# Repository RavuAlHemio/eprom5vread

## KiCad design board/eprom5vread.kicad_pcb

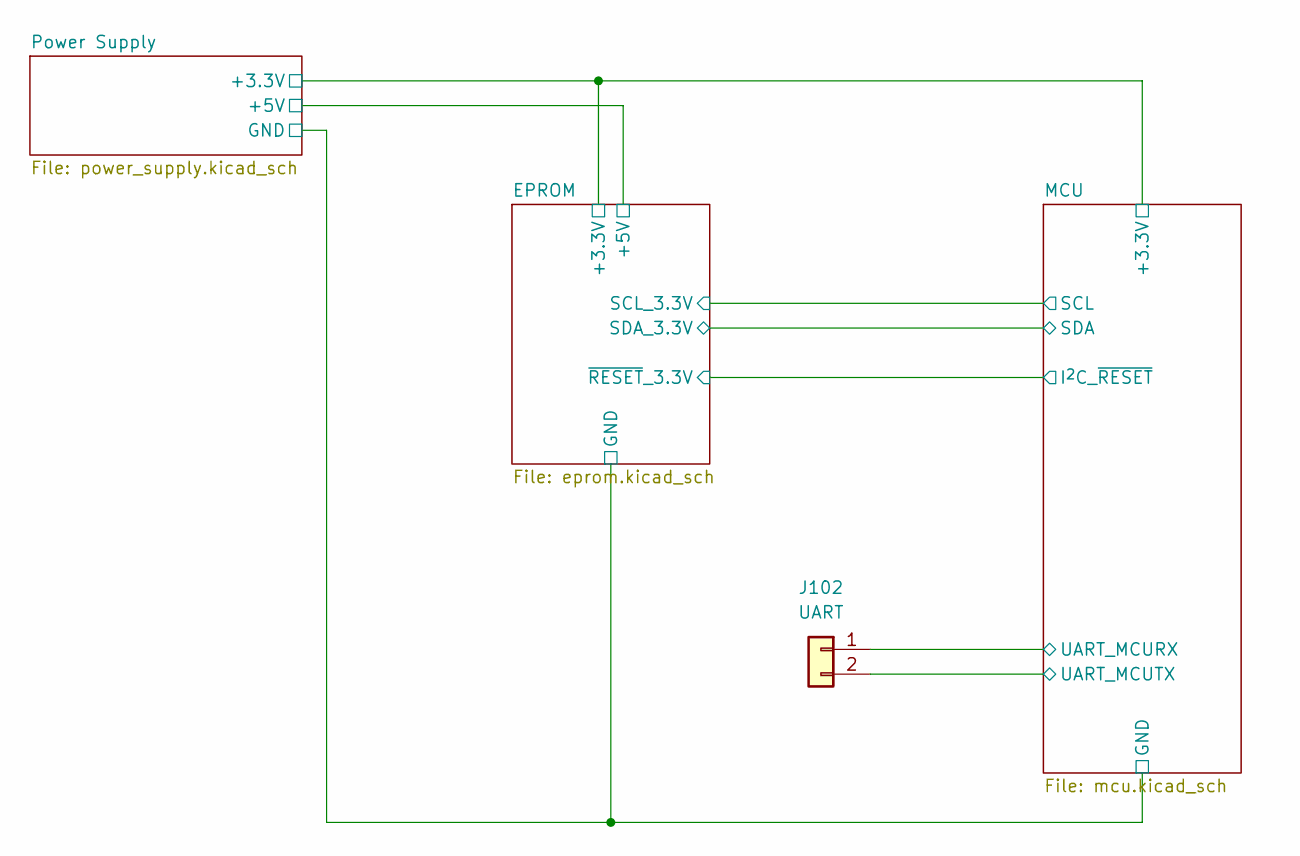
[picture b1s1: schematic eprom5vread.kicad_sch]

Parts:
J102: UART; PinHeader_2x01_P2.54mm_Vertical_SMD; LCSC C2884014

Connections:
/MCU/UART_MCURX: J102.1; also elsewhere on the board
/MCU/UART_MCUTX: J102.2; also elsewhere on the board

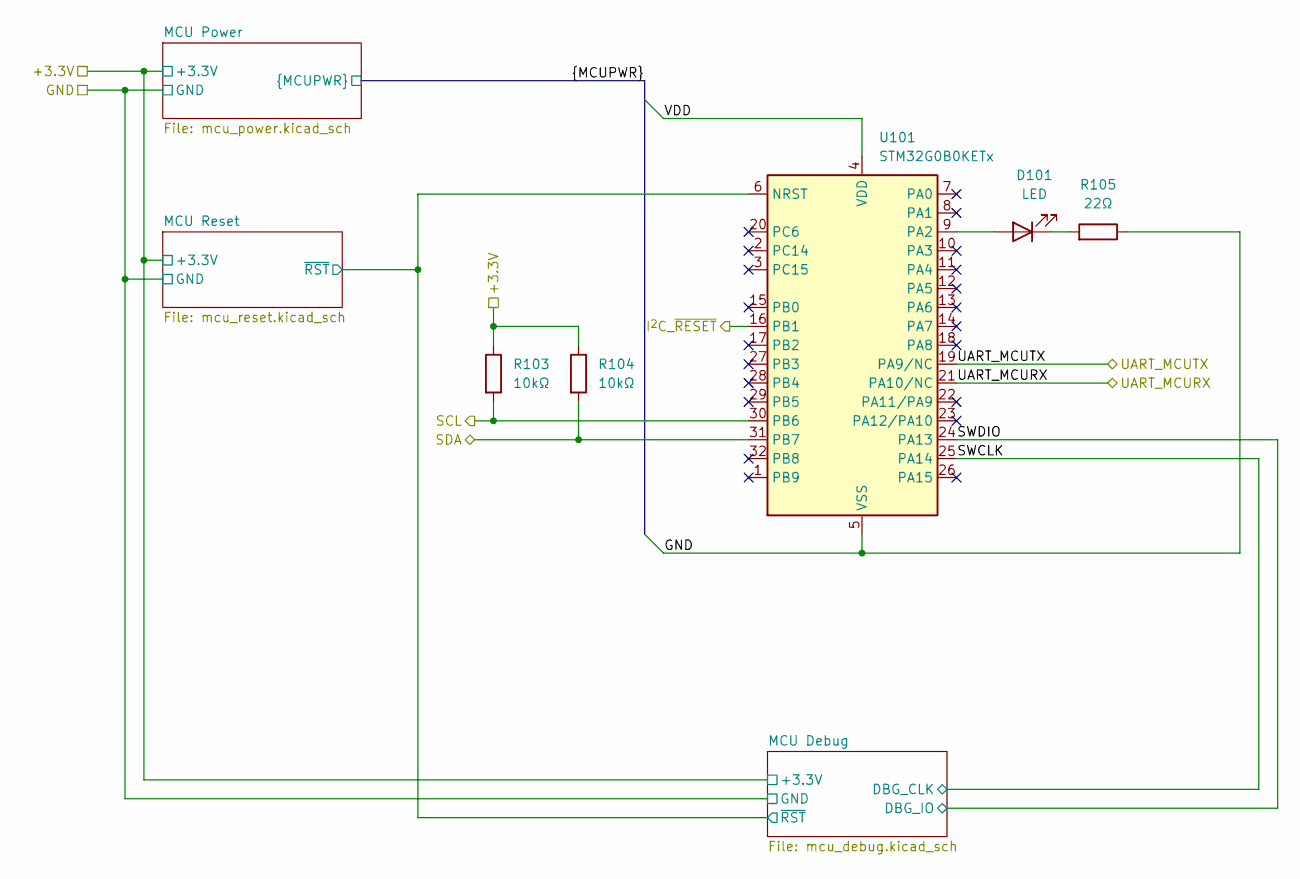
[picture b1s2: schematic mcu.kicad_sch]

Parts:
D101: LED; LED_0805_2012Metric
R103, R104: 10kΩ; R_0402_1005Metric; LCSC C25744
R105: 22Ω; R_0402_1005Metric; LCSC C25092
U101: STM32G0B0KETx; LQFP-32_7x7mm_P0.8mm; LCSC C2826978

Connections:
/EPROM/+3.3V: R103.1, R104.1; also elsewhere on the board
/EPROM/GND: R105.1, U101.5 (VSS); also elsewhere on the board
/EPROM/SCL_3.3V: R103.2, U101.30 (PB6); also elsewhere on the board
/EPROM/SDA_3.3V: R104.2, U101.31 (PB7); also elsewhere on the board
/EPROM/~RESET_3.3V: U101.16 (PB1); also elsewhere on the board
/MCU/MCU Debug/~RST: U101.6 (NRST); also elsewhere on the board
/MCU/SWCLK: U101.25 (PA14); also elsewhere on the board
/MCU/SWDIO: U101.24 (PA13); also elsewhere on the board
/MCU/UART_MCURX: U101.21 (PA10/NC); also elsewhere on the board
/MCU/UART_MCUTX: U101.19 (PA9/NC); also elsewhere on the board
/MCU/VDD: U101.4 (VDD); also elsewhere on the board
unnamed: D101.2 (A), U101.9 (PA2)
unnamed: D101.1 (K), R105.2

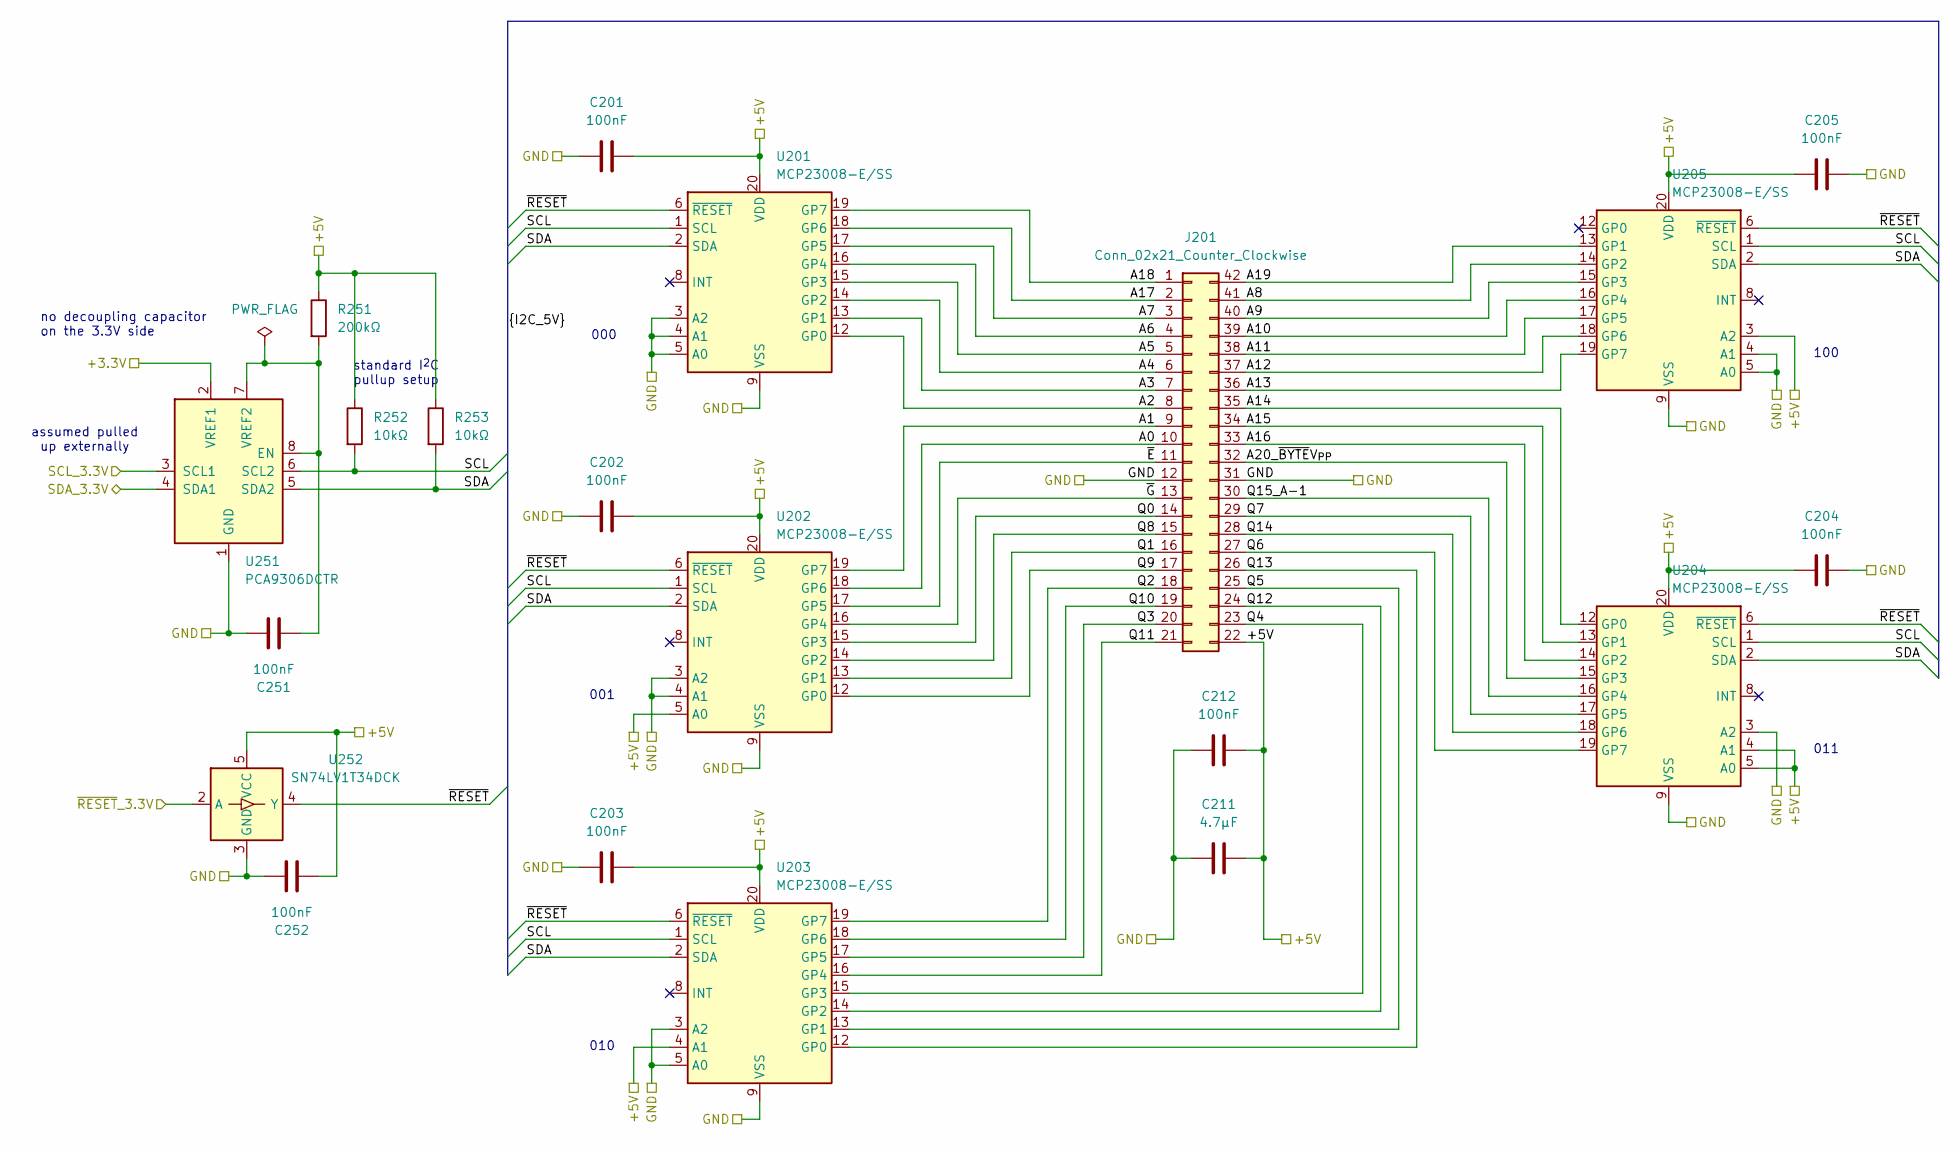
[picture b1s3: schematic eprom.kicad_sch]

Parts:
C201, C202, C203, C204, C205, C212, C251, C252: 100nF; C_0402_1005Metric; LCSC C307331
C211: 4.7µF; C_0402_1005Metric; LCSC C23733
J201: Conn_02x21_Counter_Clockwise; DIP-42_W15.24mm_Socket
R251: 200kΩ; R_0402_1005Metric; LCSC C25764
R252, R253: 10kΩ; R_0402_1005Metric; LCSC C25744
U201, U202, U203, U204, U205: MCP23008-E/SS; SSOP-20_5.3x7.2mm_P0.65mm; LCSC C148011
U251: PCA9306DCTR; SSOP-8_2.95x2.8mm_P0.65mm; LCSC C123752
U252: SN74LV1T34DCK; SOT-353_SC-70-5; LCSC C78541

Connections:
/EPROM/+3.3V: U251.2 (VREF1); also elsewhere on the board
/EPROM/+5V: C201.2, C202.2, C203.2, C204.2, C205.2, C211.2, C212.2, C252.2, J201.22, R251.1, R252.1, R253.1, U201.20 (VDD), U202.5 (A0), U202.20 (VDD), U203.4 (A1), U203.20 (VDD), U204.4 (A1), U204.5 (A0), U204.20 (VDD), U205.3 (A2), U205.20 (VDD), U252.5 (VCC); also elsewhere on the board
/EPROM/A0: J201.10, U202.18 (GP6)
/EPROM/A1: J201.9, U202.19 (GP7)
/EPROM/A2: J201.8, U201.12 (GP0)
/EPROM/A3: J201.7, U201.13 (GP1)
/EPROM/A4: J201.6, U201.14 (GP2)
/EPROM/A5: J201.5, U201.15 (GP3)
/EPROM/A6: J201.4, U201.16 (GP4)
/EPROM/A7: J201.3, U201.17 (GP5)
/EPROM/A8: J201.41, U205.14 (GP2)
/EPROM/A9: J201.40, U205.15 (GP3)
/EPROM/A10: J201.39, U205.16 (GP4)
/EPROM/A11: J201.38, U205.17 (GP5)
/EPROM/A12: J201.37, U205.18 (GP6)
/EPROM/A13: J201.36, U205.19 (GP7)
/EPROM/A14: J201.35, U204.12 (GP0)
/EPROM/A15: J201.34, U204.13 (GP1)
/EPROM/A16: J201.33, U204.14 (GP2)
/EPROM/A17: J201.2, U201.18 (GP6)
/EPROM/A18: J201.1, U201.19 (GP7)
/EPROM/A19: J201.42, U205.13 (GP1)
/EPROM/A20_~BYTEV_{PP}: J201.32, U204.15 (GP3)
/EPROM/GND: C201.1, C202.1, C203.1, C204.1, C205.1, C211.1, C212.1, C251.1, C252.1, J201.12, J201.31, U201.3 (A2), U201.4 (A1), U201.5 (A0), U201.9 (VSS), U202.3 (A2), U202.4 (A1), U202.9 (VSS), U203.3 (A2), U203.5 (A0), U203.9 (VSS), U204.3 (A2), U204.9 (VSS), U205.4 (A1), U205.5 (A0), U205.9 (VSS), U251.1 (GND), U252.3 (GND); also elsewhere on the board
/EPROM/Q0: J201.14, U202.15 (GP3)
/EPROM/Q1: J201.16, U202.13 (GP1)
/EPROM/Q2: J201.18, U203.19 (GP7)
/EPROM/Q3: J201.20, U203.17 (GP5)
/EPROM/Q4: J201.23, U203.15 (GP3)
/EPROM/Q5: J201.25, U203.13 (GP1)
/EPROM/Q6: J201.27, U204.19 (GP7)
/EPROM/Q7: J201.29, U204.17 (GP5)
/EPROM/Q8: J201.15, U202.14 (GP2)
/EPROM/Q9: J201.17, U202.12 (GP0)
/EPROM/Q10: J201.19, U203.18 (GP6)
/EPROM/Q11: J201.21, U203.16 (GP4)
/EPROM/Q12: J201.24, U203.14 (GP2)
/EPROM/Q13: J201.26, U203.12 (GP0)
/EPROM/Q14: J201.28, U204.18 (GP6)
/EPROM/Q15_A-1: J201.30, U204.16 (GP4)
/EPROM/SCL: R252.2, U201.1 (SCL), U202.1 (SCL), U203.1 (SCL), U204.1 (SCL), U205.1 (SCL), U251.6 (SCL2)
/EPROM/SCL_3.3V: U251.3 (SCL1); also elsewhere on the board
/EPROM/SDA: R253.2, U201.2 (SDA), U202.2 (SDA), U203.2 (SDA), U204.2 (SDA), U205.2 (SDA), U251.5 (SDA2)
/EPROM/SDA_3.3V: U251.4 (SDA1); also elsewhere on the board
/EPROM/~E: J201.11, U202.17 (GP5)
/EPROM/~G: J201.13, U202.16 (GP4)
/EPROM/~RESET: U201.6 (~RESET), U202.6 (~RESET), U203.6 (~RESET), U204.6 (~RESET), U205.6 (~RESET), U252.4 (Y)
/EPROM/~RESET_3.3V: U252.2 (A); also elsewhere on the board
unnamed: C251.2, R251.2, U251.7 (VREF2), U251.8 (EN)

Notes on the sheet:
standard I^{2}C pullup setup
001
no decoupling capacitor on the 3.3V side
000
011
010
100
assumed pulled up externally

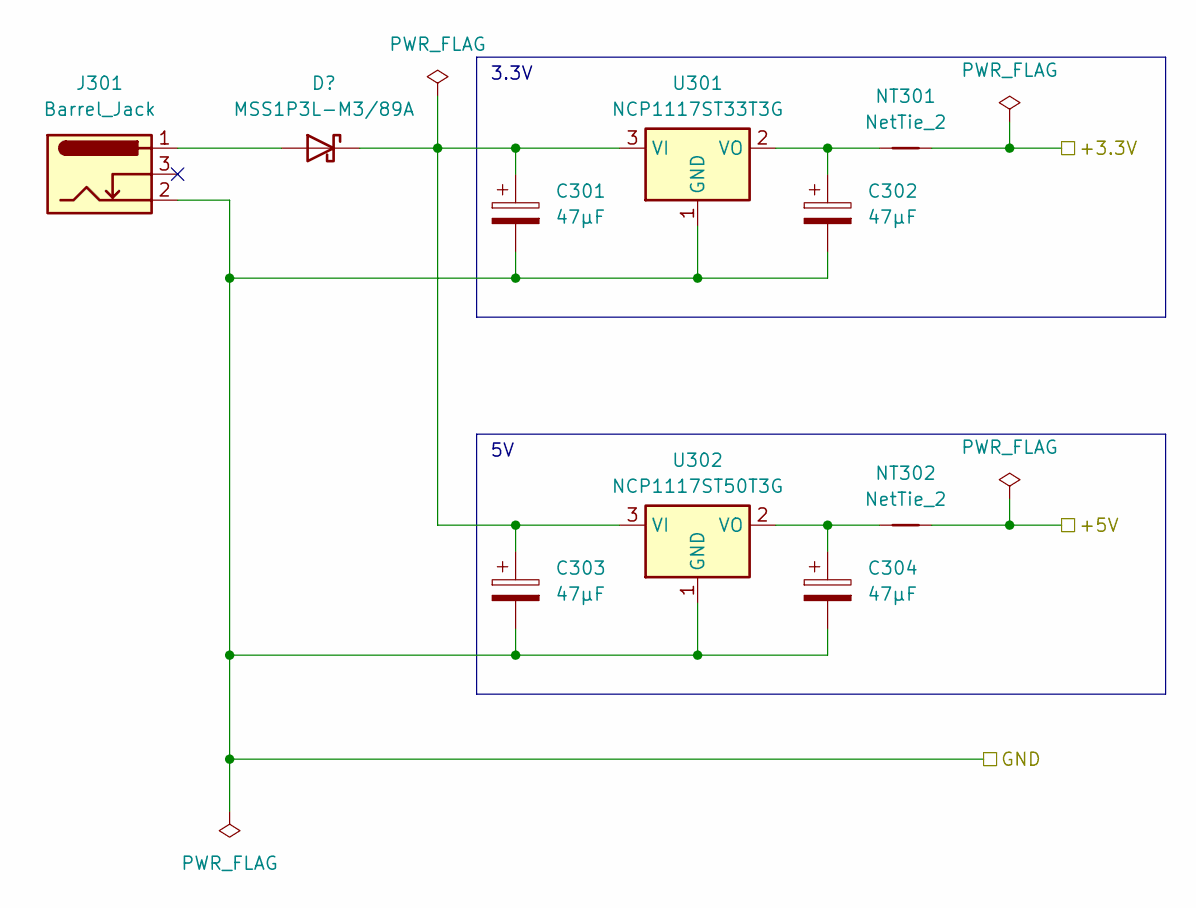
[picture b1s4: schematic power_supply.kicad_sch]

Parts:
C301, C302, C303, C304: 47µF; CP_EIA-7343-31_Kemet-D; LCSC C122333
D301: MSS1P3L-M3/89A; D_MicroSMP_AK; LCSC C144285
J301: Barrel_Jack; BarrelJack_CUI_PJ-036AH-SMT_Horizontal; LCSC C9900024875
NT301, NT302: NetTie_2; NetTie-2_SMD_Pad0.5mm
U301: NCP1117ST33T3G; SOT-223-3_TabPin2; LCSC C26537
U302: NCP1117ST50T3G; SOT-223-3_TabPin2; LCSC C17314

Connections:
/EPROM/+3.3V: NT301.2; also elsewhere on the board
/EPROM/+5V: NT302.2; also elsewhere on the board
/EPROM/GND: C301.2, C302.2, C303.2, C304.2, J301.2, U301.1 (GND), U302.1 (GND); also elsewhere on the board
unnamed: D301.2 (A), J301.1
unnamed: C301.1, C303.1, D301.1 (K), U301.3 (VI), U302.3 (VI)
unnamed: C302.1, NT301.1, U301.2 (VO)
unnamed: C304.1, NT302.1, U302.2 (VO)

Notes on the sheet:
3.3V

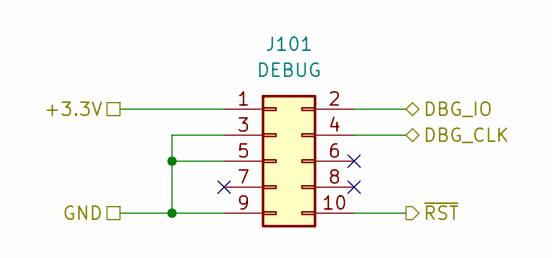
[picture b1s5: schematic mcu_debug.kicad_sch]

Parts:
J101: DEBUG; PinHeader_2x05_P1.27mm_Vertical_SMD; LCSC C5250218

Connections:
/EPROM/+3.3V: J101.1; also elsewhere on the board
/EPROM/GND: J101.3, J101.5, J101.9; also elsewhere on the board
/MCU/MCU Debug/~RST: J101.10; also elsewhere on the board
/MCU/SWCLK: J101.4; also elsewhere on the board
/MCU/SWDIO: J101.2; also elsewhere on the board

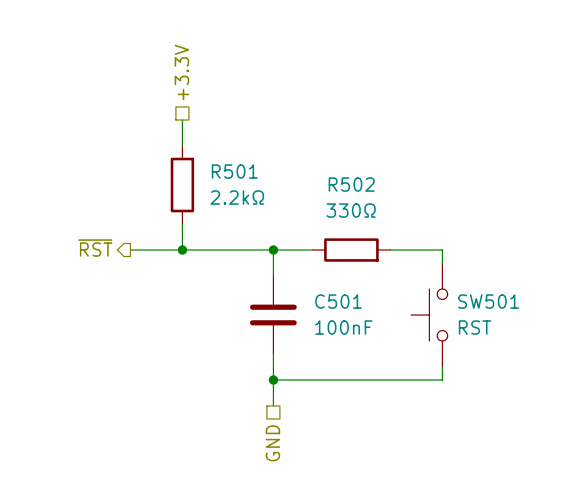
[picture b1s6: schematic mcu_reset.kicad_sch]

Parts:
C501: 100nF; C_0402_1005Metric; LCSC C307331
R501: 2.2kΩ; R_0402_1005Metric; LCSC C25879
R502: 330Ω; R_0402_1005Metric; LCSC C25104
SW501: RST; SW_Push_1P1T_XKB_TS-1187A; LCSC C318884

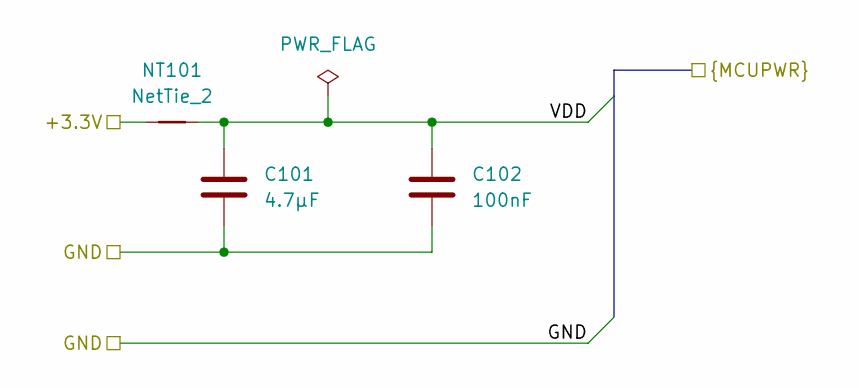
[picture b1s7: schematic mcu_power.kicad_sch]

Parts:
C101: 4.7µF; C_0402_1005Metric; LCSC C23733
C102: 100nF; C_0402_1005Metric; LCSC C307331
NT101: NetTie_2; NetTie-2_SMD_Pad0.5mm

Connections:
/EPROM/+3.3V: NT101.1; also elsewhere on the board
/EPROM/GND: C101.2, C102.2; also elsewhere on the board
/MCU/VDD: C101.1, C102.1, NT101.2; also elsewhere on the board

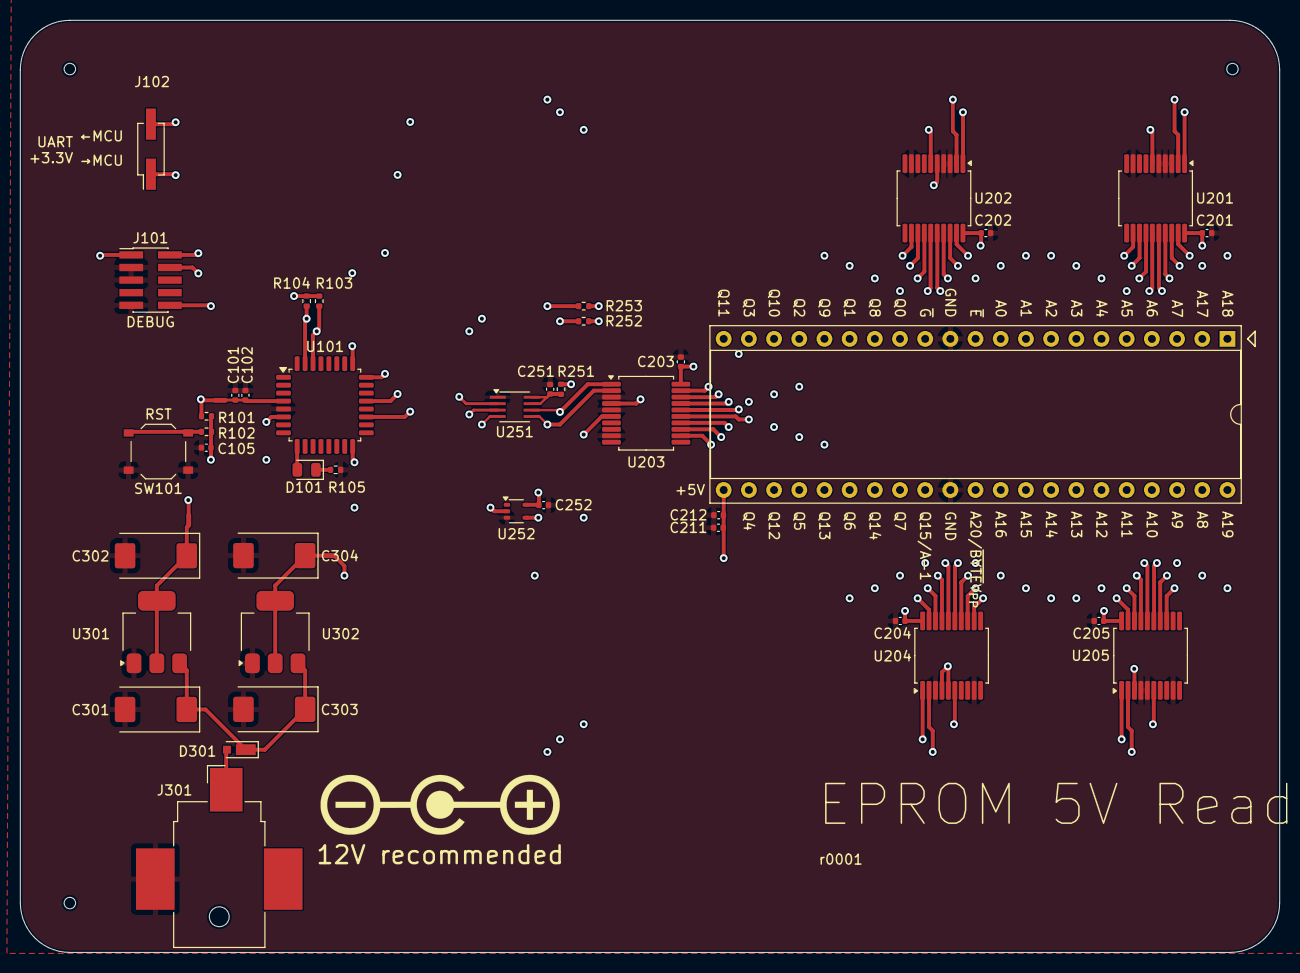
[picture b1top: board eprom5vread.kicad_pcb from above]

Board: 4 copper layers, 127.0 x 94.0 mm, 48 parts (0 on the bottom side), 62 nets.

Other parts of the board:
C105: 100nF; C_0402_1005Metric
R101: 2.2kΩ; R_0402_1005Metric
R102: 330Ω; R_0402_1005Metric
REF1, REF2, REF3: JLCPCB_Mounting_Hole
REF4: Polarity_Center_Positive_6mm_SilkScreen
SW101: RST; SW_Push_1P1T_XKB_TS-1187A

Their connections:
/EPROM/+3.3V: R101.2; also elsewhere on the board
/EPROM/GND: C105.1, SW101.1; also elsewhere on the board
/MCU/MCU Debug/~RST: C105.2, R101.1, R102.1; also elsewhere on the board
unnamed: R102.2, SW101.2

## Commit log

2024-01-29 initial commit (WIP board)
2024-01-29 initial board layout (WIP), schematic tuning
2024-01-30 finish board design
2024-02-01 pcb: add ROM pin hints
2024-02-01 initial work on code
2024-02-02 code: UART initialization
2024-02-02 pins: clarify what leads to ROM and what not
2024-02-02 add Unix stm32g0b0 regeneration script
2024-02-02 code: finish reading algorithm
2024-03-22 redo board to use I2C port expanders (and smaller MCU)
2024-03-22 allow driving ~RESET pins of I2C I/O expanders, add missing resistors
2024-03-22 improve locations of some labels
2024-03-22 ignore lock and JLCPCB manufacturing files
2024-03-22 update pin overview
2024-03-22 update MCU model name
    we use the variant with fewer pins now
2024-03-22 add an LED because everything is better with LEDs
    also debugging before UART comes up
2024-03-22 pins: document pins on I/O expander
2024-03-22 rewrite code to use I/O expanders
2024-03-22 set up LED
2024-03-22 reset port expanders on boot
